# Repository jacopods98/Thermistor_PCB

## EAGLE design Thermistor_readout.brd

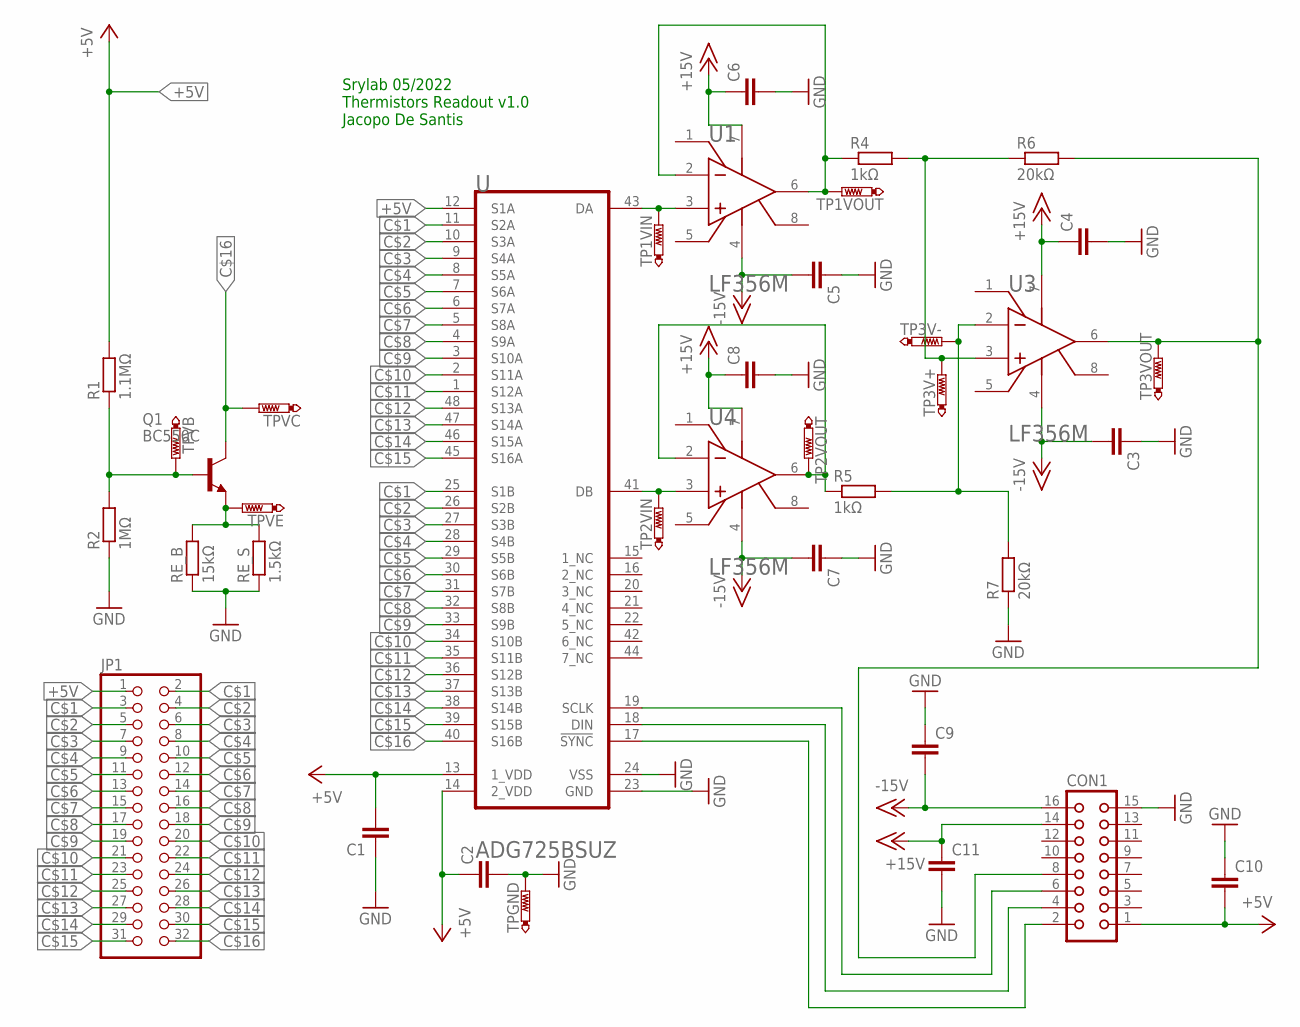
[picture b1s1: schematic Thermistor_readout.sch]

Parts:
C1, C2, C3, C4, C5, C6, C7, C8: C-EU_SMDR1206H; R1206H
C9, C10, C11: C-EU_SMDC1206H/D; C1206H/D
CON1: CON16L
JP1: PINHD-2X16; 2X16
Q1: BC550C; TO92-EBC
R1: 1.1ΜΩ; R0805H
R2: 1ΜΩ; R0805H
R4, R5: 1kΩ; R0805H
R6, R7: 20kΩ; R0805H
RE_B: 15kΩ; R1206H
RE_S: 1.5kΩ; R0805H
TP1VIN, TP1VOUT, TP2VIN, TP2VOUT, TP3V+, TP3V-, TP3VOUT: PTR1TP20R; TP20R
TPGND: PTR1TP20R; TP20R
TPVB: PTR1TP20R; TP20R
TPVC: PTR1TP20R; TP20R
TPVE: PTR1TP20R; TP20R
U: ANALOG_DEVICES_ADG725BSUZANALOG_DEVICES_ADG725BSU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; ANALOG_DEVICES_ADG725BSUZ_2
U1, U3, U4: TI_NATIONAL_SEMICONDUCTOR_LF356MTI_NATIONAL_SEMIC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; TI_NATIONAL_SEMICONDUCTOR_LF356M_2

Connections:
+5V: C1.2, C2.1, C10.2, CON1.1, JP1.1, R1.2, U.12 (S1A), U.13 (1_VDD), U.14 (2_VDD)
+15V: C4.1, C6.1, C8.1, C11.1, CON1.14, U1.7 (V+), U3.7 (V+), U4.7 (V+)
-15V: C3.2, C5.2, C7.2, C9.2, CON1.16, U1.4 (V-), U3.4 (V-), U4.4 (V-)
C$1: JP1.2, JP1.3, U.11 (S2A), U.25 (S1B)
C$2: JP1.4, JP1.5, U.10 (S3A), U.26 (S2B)
C$3: JP1.6, JP1.7, U.9 (S4A), U.27 (S3B)
C$4: JP1.8, JP1.9, U.8 (S5A), U.28 (S4B)
C$5: JP1.10, JP1.11, U.7 (S6A), U.29 (S5B)
C$6: JP1.12, JP1.13, U.6 (S7A), U.30 (S6B)
C$7: JP1.14, JP1.15, U.5 (S8A), U.31 (S7B)
C$8: JP1.16, JP1.17, U.4 (S9A), U.32 (S8B)
C$9: JP1.18, JP1.19, U.3 (S10A), U.33 (S9B)
C$10: JP1.20, JP1.21, U.2 (S11A), U.34 (S10B)
C$11: JP1.22, JP1.23, U.1 (S12A), U.35 (S11B)
C$12: JP1.24, JP1.25, U.36 (S12B), U.48 (S13A)
C$13: JP1.26, JP1.27, U.37 (S13B), U.47 (S14A)
C$14: JP1.28, JP1.29, U.38 (S14B), U.46 (S15A)
C$15: JP1.30, JP1.31, U.39 (S15B), U.45 (S16A)
C$16: JP1.32, Q1.C, TPVC.TP, U.40 (S16B)
GND: C1.1, C2.2, C3.1, C4.2, C5.1, C6.2, C7.1, C8.2, C9.1, C10.1, C11.2, CON1.15, R2.1, R7.1, RE_B.1, RE_S.1, TPGND.TP, U.23 (GND), U.24 (VSS)
unnamed: Q1.B, R1.1, R2.2, TPVB.TP
unnamed: Q1.E, RE_B.2, RE_S.2, TPVE.TP
unnamed: TP2VIN.TP, U.41 (DB), U4.3 (IN+)
unnamed: R4.1, TP1VOUT.TP, U1.2 (IN-), U1.6 (OUT)
unnamed: R5.2, R7.2, TP3V-.TP, U3.2 (IN-)
unnamed: R4.2, R6.1, TP3V+.TP, U3.3 (IN+)
unnamed: TP1VIN.TP, U.43 (DA), U1.3 (IN+)
unnamed: R5.1, TP2VOUT.TP, U4.2 (IN-), U4.6 (OUT)
unnamed: CON1.6, U.19 (SCLK)
unnamed: CON1.2, U.17 (!SYNC!)
unnamed: CON1.4, U.18 (DIN)
unnamed: CON1.8, R6.2, TP3VOUT.TP, U3.6 (OUT)

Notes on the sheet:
Srylab 05/2022 Thermistors Readout v1.0 Jacopo De Santis

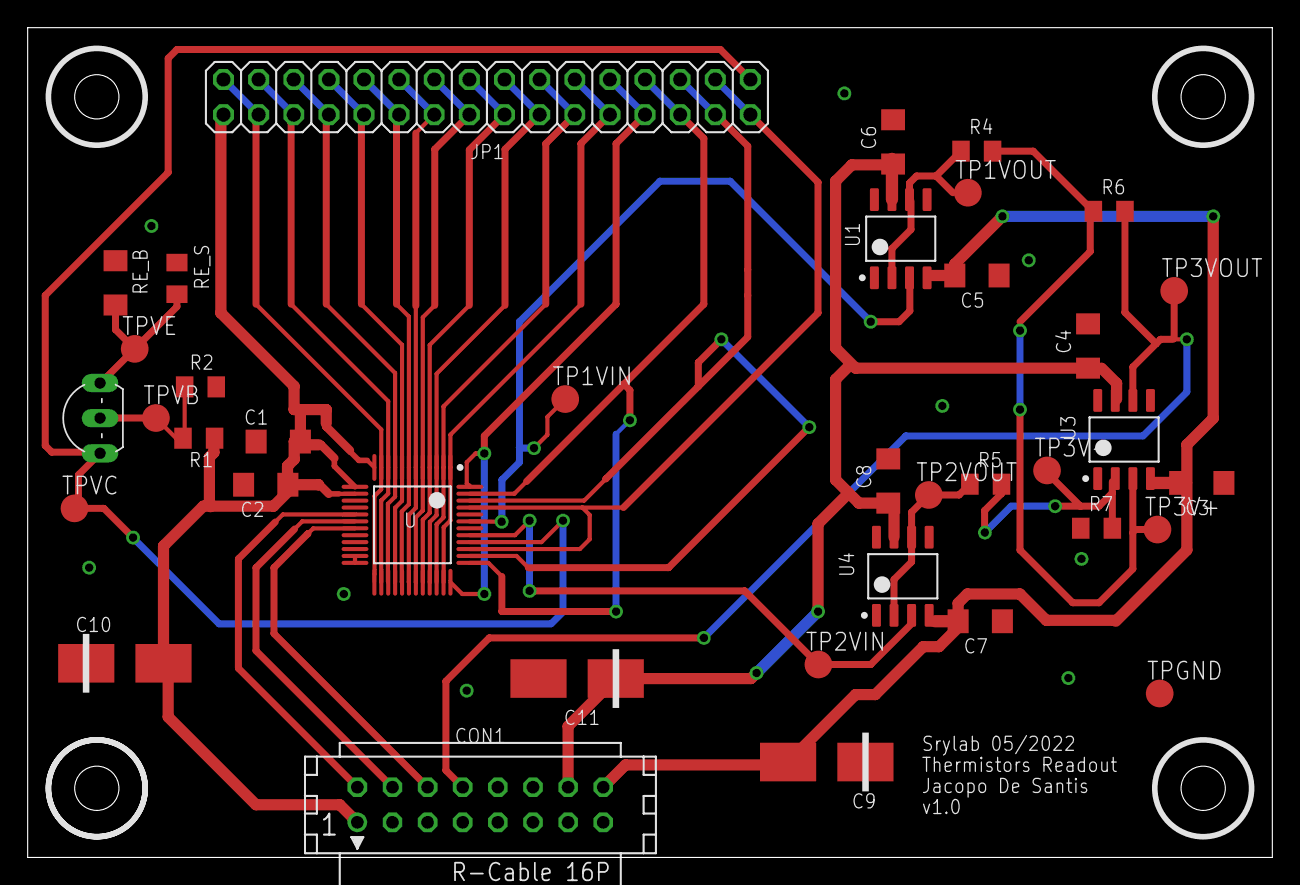
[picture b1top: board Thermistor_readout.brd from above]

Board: 2 copper layers, 90.0 x 60.0 mm, 37 parts (0 on the bottom side), 32 nets.

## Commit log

2022-02-21 initialization
2022-02-21 New_Re_size
2022-02-22 First_PCB_tentative
2022-02-22 Simil_complete1
2022-02-22 finished_1st_version
2022-02-22 No_error_v1
2022-02-22 first_print_v1.0
2022-02-22 final_v1.0
2022-02-22 NewSchematicV1.1
2022-02-22 Internal_switch_v1.1
2022-02-22 Finished_v1.1
2022-02-22 Before_corrections_v1.1
2022-02-23 new_connector
2022-03-09 Fix_missing_m15V_connection
2022-03-10 Updated_Flat_cable_connections
2022-03-15 Stable_version_J_Mac
2022-03-15 Re_0805_size
2022-03-15 Lab_PC_v1
2022-03-16 double sized Re resistor
2022-03-18 1206_capacitors
2022-03-22 final_print
2022-03-23 ready_to_print
2022-06-08 production
